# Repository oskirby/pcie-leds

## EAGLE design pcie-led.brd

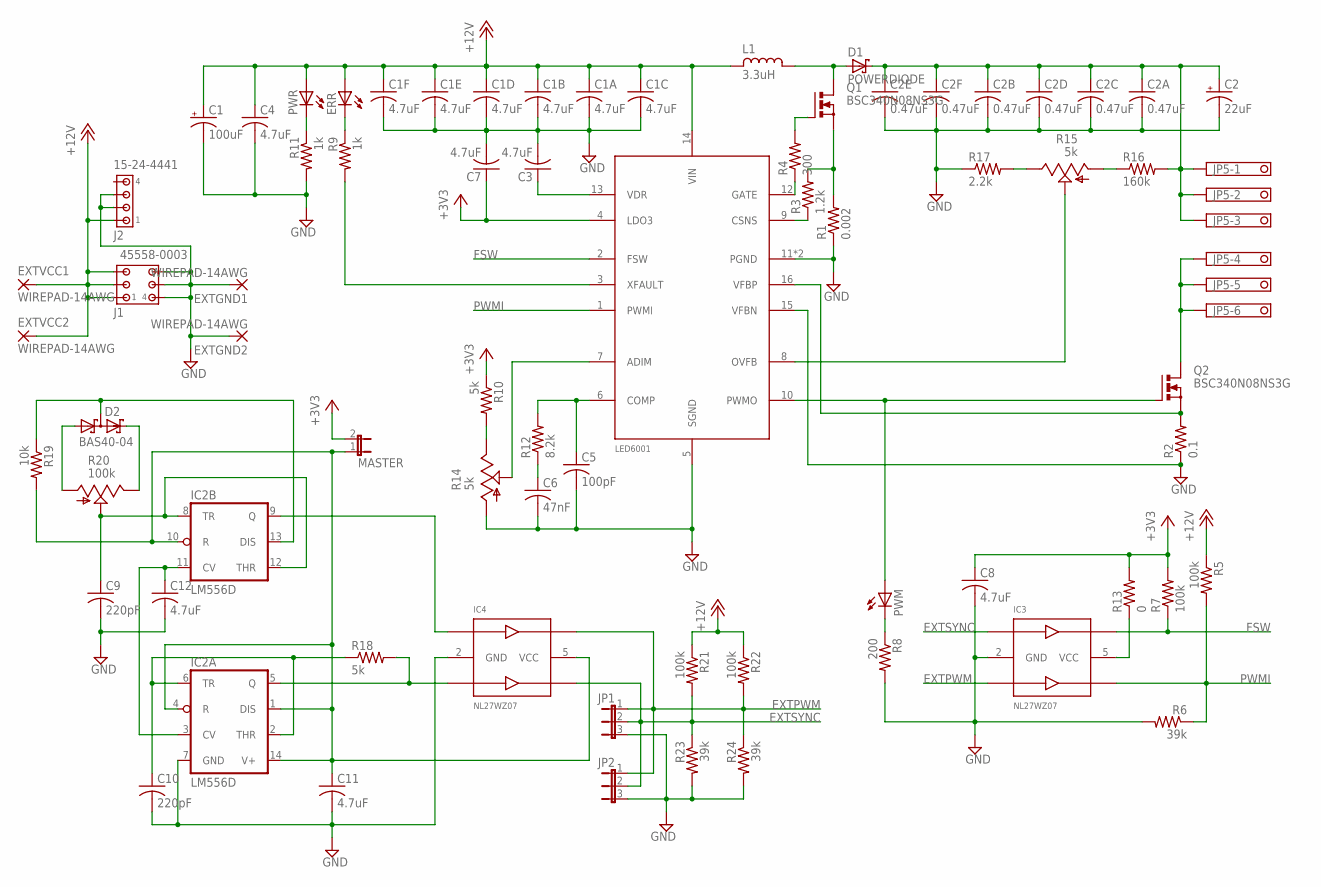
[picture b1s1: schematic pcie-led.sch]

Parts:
C1: 100uF; E3,5-8
C1A, C1B, C1C, C1D, C1E, C1F: 4.7uF; C0805
C2: 22uF; E3,5-8
C2A, C2B, C2C, C2D, C2E, C2F: 0.47uF; C0805
C3, C4, C7, C8, C11, C12: 4.7uF; C0603
C5: 100pF; C0603
C6: 47nF; C0603
C9, C10: 220pF; C0603
D1: POWERDIODE; LFPACK56-TO277
D2: BAS40-04; SOT23
ERR: LEDCHIP-LED0805; CHIP-LED0805
EXTGND1, EXTGND2: WIREPAD-14AWG
EXTVCC1, EXTVCC2: WIREPAD-14AWG
IC1: LED6001; HTSSOP-16
IC2: LM556D; SO14
IC3, IC4: NL27WZ07; SOT363
J1: 45558-0003
J2: 15-24-4441
JP1, JP2: JP2E; JP2
JP5: OSTTE06
L1: 3.3uH; SRP1770TA
MASTER: JP1E; JP1
PWM: LEDCHIP-LED0805; CHIP-LED0805
PWR: LEDCHIP-LED0805; CHIP-LED0805
Q1, Q2: BSC340N08NS3G; PG-TDSON-8
R1: 0.002; R1206
R2: 0.1; R2512
R3: 1.2k; R0603
R4: 300; R0603
R5, R7, R21, R22: 100k; R0603
R6, R23, R24: 39k; R0603
R8: 200; R0603
R9, R11: 1k; R0603
R10, R18: 5k; R0603
R12: 8.2k; R0603
R13: 0; R0603
R14, R15: 5k; ST-4EB
R16: 160k; R0603
R17: 2.2k; R0603
R19: 10k; R0603
R20: 100k; P260T

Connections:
+3V3: C7.1, C8.1, IC1.4 (LDO3), MASTER.2, R7.2, R10.1, R13.2
+12V: C1.+, C1A.1, C1B.1, C1C.1, C1D.1, C1E.1, C1F.1, C4.1, ERR.A, EXTVCC1.TP, EXTVCC2.TP, IC1.14 (VIN), J1.1, J1.2, J1.3, J2.1, L1.P$1 (1), PWR.A, R5.1, R21.1, R22.1
CSNS: Q1.1 (S), Q1.2 (S), Q1.3 (S), R1.2, R3.2
EXTPWM: IC3.3 (IN2), IC4.6 (OUT1), JP1.1, JP2.1, R22.2, R24.1
EXTSYNC: IC3.1 (IN1), IC4.4 (OUT2), JP1.2, JP2.2, R21.2, R23.1
FSW: IC1.2 (FSW), IC3.6 (OUT1), R7.1
GND: C1.-, C1A.2, C1B.2, C1C.2, C1D.2, C1E.2, C1F.2, C2.-, C2A.2, C2B.2, C2C.2, C2D.2, C2E.2, C2F.2, C3.2, C4.2, C5.2, C6.2, C7.2, C8.2, C9.2, C10.2, C11.2, C12.2, EXTGND1.TP, EXTGND2.TP, IC1.5 (SGND), IC1.11 (PGND), IC1.15 (VFBN), IC1.PAD (PGND), IC2.7 (GND), IC3.2 (GND), IC4.2 (GND), J1.4, J1.5, J1.6, J2.2, J2.3, JP1.3, JP2.3, R1.1, R2.1, R6.2, R8.2, R11.2, R14.1 (A), R17.1, R23.2, R24.2
L+: D1.A, L1.P$2 (4), Q1.5 (D), Q1.6 (D), Q1.7 (D), Q1.8 (D), Q1.TH (D)
LED+: C2.+, C2A.1, C2B.1, C2C.1, C2D.1, C2E.1, C2F.1, D1.C1 (C), D1.C2 (C), D1.C3 (C), D1.C4 (C), D1.TH (C), JP5.1, JP5.2, JP5.3, R16.2
LED-: JP5.4, JP5.5, JP5.6, Q2.5 (D), Q2.6 (D), Q2.7 (D), Q2.8 (D), Q2.TH (D)
unnamed: PWM.C, R8.1
unnamed: IC1.10 (PWMO), PWM.A, Q2.4 (G)
unnamed: Q1.4 (G), R4.2
unnamed: C11.1, IC2.1 (DIS), IC2.4 (R), IC2.10 (R), IC2.14 (V+), IC4.5 (VCC), MASTER.1, R19.2
unnamed: IC1.12 (GATE), R4.1
unnamed: IC2.5 (Q), IC4.3 (IN2), R18.2
unnamed: R15.1 (A), R16.1
unnamed: IC2.9 (Q), IC4.1 (IN1)
unnamed: C5.1, IC1.6 (COMP), R12.2
unnamed: C6.1, R12.1
unnamed: IC1.8 (OVFB), R15.2 (S)
unnamed: IC1.7 (ADIM), R14.2 (S)
unnamed: R15.3 (E), R17.2
unnamed: R10.2, R14.3 (E)
unnamed: IC1.9 (CSNS), R3.1
unnamed: IC3.5 (VCC), R13.1
unnamed: C12.1, IC2.3 (CV), IC2.11 (CV)
unnamed: C10.1, IC2.2 (THR), IC2.6 (TR), R18.1
unnamed: ERR.C, R9.1
unnamed: D2.2 (C2), R20.3 (E)
unnamed: D2.1 (A1), R20.1 (A)
unnamed: C9.1, IC2.8 (TR), IC2.12 (THR), R20.2 (S)
unnamed: D2.3 (C1A2), IC2.13 (DIS), R19.1
unnamed: PWR.C, R11.1
unnamed: C3.1, IC1.13 (VDR)
PWMI: IC1.1 (PWMI), IC3.4 (OUT2), R5.2, R6.1
VFBP: IC1.16 (VFBP), Q2.1 (S), Q2.2 (S), Q2.3 (S), R2.2
XFAULT: IC1.3 (XFAULT), R9.2

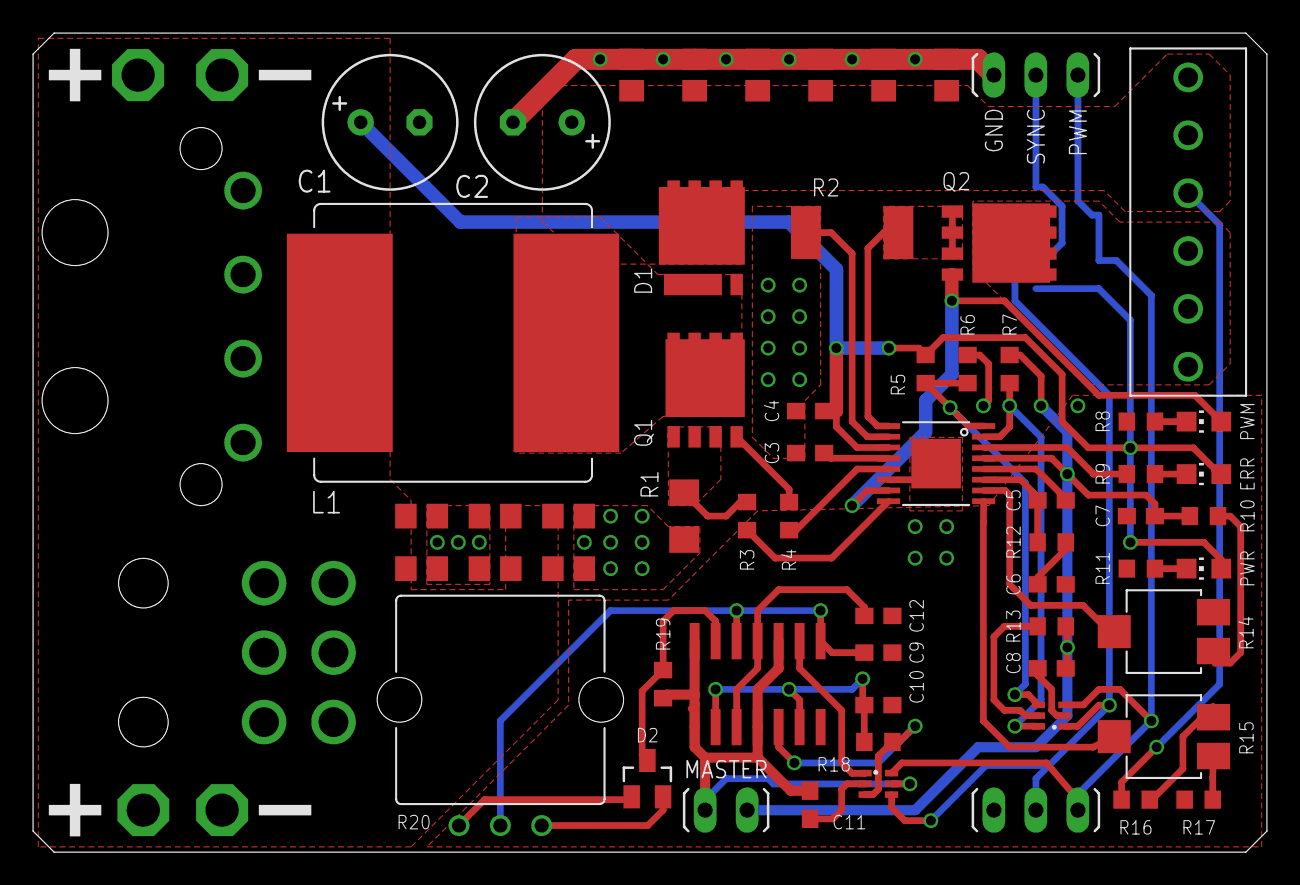
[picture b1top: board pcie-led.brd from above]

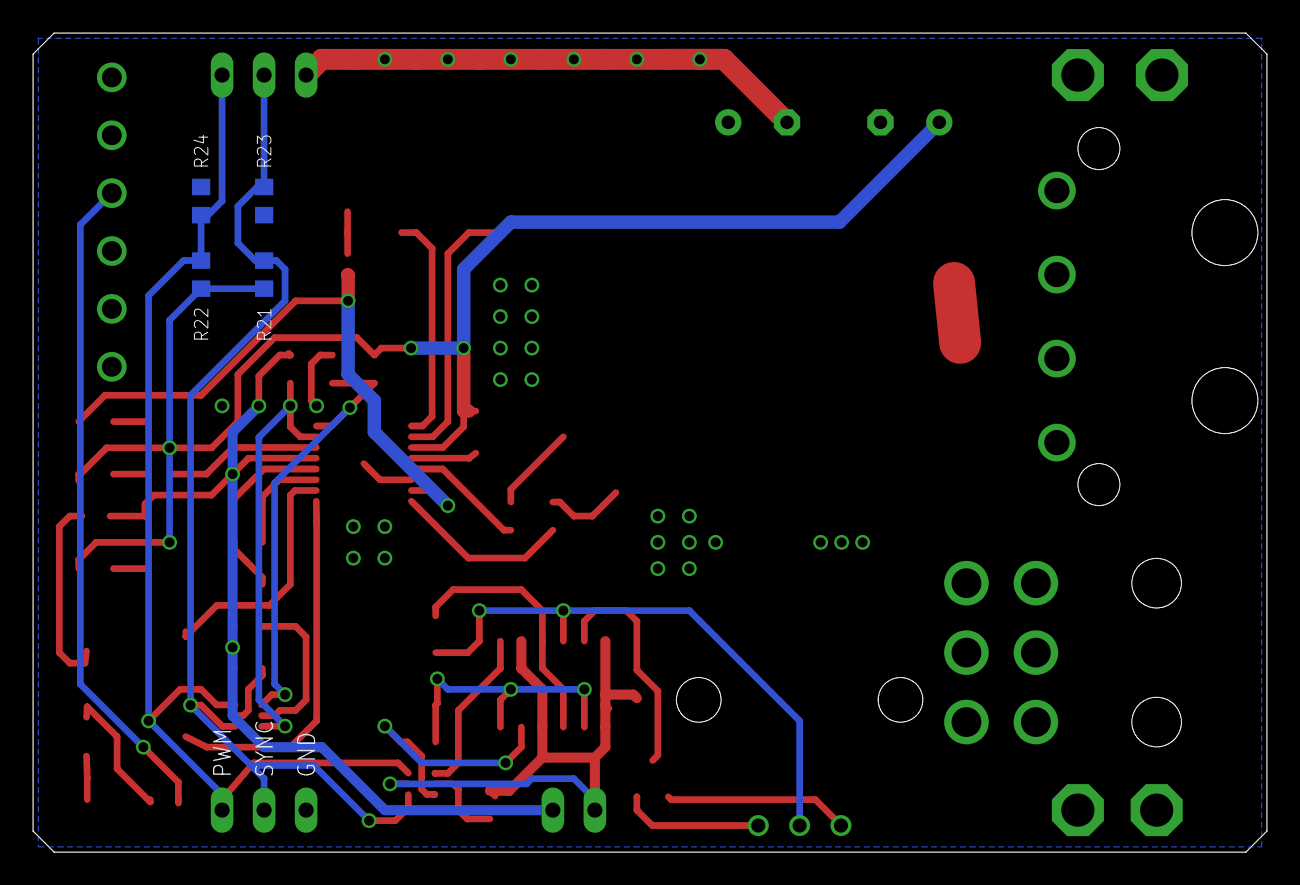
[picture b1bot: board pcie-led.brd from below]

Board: 2 copper layers, 74.6 x 49.5 mm, 70 parts (4 on the bottom side), 38 nets.

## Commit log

2016-11-22 Initial import
2016-11-22 Add board layout
2016-11-23 Fix errors with clock and PWM generators
2016-11-23 Add variant with high-side current sensing.
2016-11-23 Tweaks for DRC, and shrink board <5cm width
2016-11-23 Add missing pci-led.sch from last commit.
2016-11-23 Release to manufacturing
2016-11-28 BOM and supplier information
